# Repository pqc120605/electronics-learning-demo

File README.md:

# Mạch Mở — demo học Điện tử, Nhúng và IoT

Mạch Mở là website học miễn phí cho người mới. Khách có thể xem bài học, khám phá mô hình mạch 3D tương tác và thử đổi nhịp LED trong bài ESP32 mà không cần tài khoản. Khu `/admin` dành cho founder để xem thống kê phiên truy cập và tương tác.

## Trang công khai và không gian học

- Quyết định kiến trúc về dữ liệu dùng chung nằm trong [ADR 0001 · Node API tự quản](docs/adr/0001-backend-duy-nhat-node-api.md).
- `/` là trang giới thiệu thế giới điện tử và các tính năng của Mạch Mở.
- `/app` là dashboard học tập dành cho khách, dẫn tới bài học, thư viện board/linh kiện, bàn lắp mạch, chủ đề, công cụ và dự án đang có.
- App workspace là một bề mặt guest-first chạy chung SPA React/Vite với website. Đây chưa phải native app. Service worker cache app shell cùng các JS/CSS đã tải để mở lại một số route khi offline; không cache model 3D lớn, firmware hay API, và chưa có đồng bộ offline.
- Bản đồ sản phẩm Web/App, ranh giới dữ liệu, simulator providers, công cụ GitHub đã khảo sát và lộ trình nền tảng được mô tả trong [`docs/mach-mo-final-web-app-framework.md`](../docs/mach-mo-final-web-app-framework.md).
- Route chuẩn nằm trong `src/data/productRoutes.ts`; feature, trạng thái và nhãn menu dùng chung nằm ở `src/data/productFeatureRegistry.ts`. URL legacy như `/boards` và `/build` vẫn được giữ để tương thích; các đường dẫn app có namespace `/app/...`.
- Hợp đồng chuẩn hóa cho simulation provider nằm tại `src/simulation/contracts.ts`. Các bài học dùng interpreter giáo dục giới hạn trong `src/lib/simulationProviders.ts`; công cụ SPICE dùng `eecircuit-engine`/ngspice WASM trong Web Worker. Workspace có handoff cho subset analog khi dây, node và trị số thỏa mapping hỗ trợ; compiler từ chối MCU/GPIO và phần tử chưa có model. Đây không phải chuyển đổi mọi bài/schematic, không lấy copper PCB làm netlist và không thay provider firmware.
- Luồng CAD có báo cáo đối chiếu tất cả chân có net trong KiCad schematic với PCB IPC-D-356 theo ref/pin và nhóm kết nối; giữ rõ chân NC và bỏ qua record via khi đếm chân. Sau đó, đường tạo netlist SPICE vẫn chỉ ánh xạ R/C/L/V hỗ trợ và yêu cầu loại trừ tường minh phần tử khác. Xem [hướng dẫn nhập KiCad vào SPICE](docs/kicad-to-spice-import.md); đối chiếu CAD không xác nhận file cùng revision hoặc board sản xuất, và PCB đơn lẻ không tự trở thành mô hình điện.
- Các URL chức năng hiện tại như `/learn/esp32-led`, `/boards`, `/components`, `/build`, `/topics`, `/projects` và `/tools/firmware-hex` vẫn dùng trực tiếp được.
- Dashboard `/app` và trang `/topics` hiển thị lộ trình 4 chặng gồm đủ 11 bài (`src/data/learningPath.ts`); bài LED mở trang dài `/learn/esp32-led`, 10 bài còn lại mở trang chuẩn bị `/learn/<id>` với mục tiêu, board, bảng chân, vật tư và mức mô phỏng trước khi vào phòng thử. Thứ tự này cũng quyết định "bài tiếp theo" trong phòng thử. Sơ đồ nguyên lý có danh sách net nối dây; chọn net tô sáng các kết nối tương ứng trên schematic và cảnh lắp. Net ở đây chỉ là topology workspace, không phải ERC, kết quả điện hay copper của PCB tham chiếu. Board profile hiển thị các link tài liệu/ảnh/CAD được khai báo cho đúng mẫu và revision; link nguồn là bằng chứng tham khảo, không xác minh board vật lý người học đang cầm. Bài vừa mở và checklist tự xác nhận của bài LED được lưu cục bộ; đây không phải tiến độ kỹ năng đã xác minh và không đồng bộ tài khoản.
- Cả 11 bài thực hành đều có deep link `?lesson=<id>`, ví dụ `/build?lesson=button-led&guided=1`; khi mở từ `/app`, liên kết nội bộ giữ namespace app. Link bài mở phiên riêng theo tab trong `sessionStorage`, tiếp tục bản nháp của phiên nếu có và không thay workspace `/build` trong `localStorage`. Link `?board=` chỉ đề xuất đổi board khi đã có workspace.
- Công cụ **Kiểm tra firmware HEX** đọc tệp Intel HEX ngay trong trình duyệt, kiểm tra checksum/địa chỉ/kích thước và hiển thị các vùng dữ liệu. Có firmware assembly mẫu và HEX do Arduino IDE 2.3.10 + Arduino AVR Boards 1.8.8 biên dịch từ sketch Uno; AVR8js cho chọn Uno R3 hoặc Nano classic, yêu cầu xác nhận target ATmega328P và chạy tối đa một giây để quan sát GPIO D13/PB5. Tệp người dùng chọn không tải lên máy chủ; target không nhận dạng tự động; web không compile sketch Arduino hay upload, và các board MCU khác chưa được hỗ trợ.
- Trong workspace `/build`, panel **Kết quả đến từ đâu?** phân biệt trace của mô hình bài học với lần chạy HEX AVR8js và waveform trả về từ SPICE. Chế độ HEX là tùy chọn riêng, chỉ nhận Uno R3/Nano classic ATmega328P sau khi người dùng xác nhận target; chỉ hiển thị D13/PB5 và UART0, không ánh xạ lên LED ngoài trên canvas. Kết quả SPICE chỉ quay lại cùng revision workspace trong phiên tab; sửa board, bài, code hoặc dây sẽ dừng/loại kết quả cũ. Đây là quan sát từ provider riêng, không phải đồng mô phỏng firmware–SPICE hay điện áp đo trên board.
- Web manifest cung cấp tên ứng dụng, màu giao diện, biểu tượng và điểm mở `/app`. Tùy trình duyệt và thiết bị, người dùng có thể cài website như một ứng dụng web.
- Cache offline hiện chỉ giữ app shell và tài nguyên cùng origin đã tải. Lần đầu cần có mạng để cài cache; engine SPICE lớn được tải khi mở/chạy công cụ và khả năng dùng offline phụ thuộc cache của trình duyệt. Chưa có tài khoản học viên hay chạy firmware MCU tổng quát.

## Chạy trên máy

Yêu cầu Node.js tương thích với Vite 8.

```powershell
cd D:\StartupOS\electronics-learning-demo
npm.cmd install
npm.cmd run dev -- --host 127.0.0.1 --port 5173 --strictPort --open /build
```

Lệnh luôn dùng `http://127.0.0.1:5173/build`; nếu cổng 5173 đang bận, Vite báo lỗi thay vì âm thầm chuyển sang cổng khác. Đóng cửa sổ terminal đang chạy một bản Mach Mở cũ rồi thử lại. Giữ terminal mở khi dùng web; dừng server bằng `Ctrl+C`.

Trên Windows, có thể chạy `start-demo.cmd` bằng cách nhấp đúp. Script dùng `npm.cmd` để tránh lỗi PowerShell chặn `npm.ps1`, rồi mở workspace `/build` ở cổng cố định. Giữ cửa sổ terminal mở trong lúc dùng; đóng server bằng `Ctrl+C`.

`npm.cmd run build` chạy cổng kiểm tra phân phối trước khi tạo bản production. Ngspice WASM nay được tự build từ nguồn đã ghim; hồ sơ review gắn với hash nằm trong `public/licenses/spice-engine-provenance.json`. Dùng `npm.cmd run build:public` cho bản phát hành và giữ toàn bộ thư mục license/source/relink trong output. `build:local` vẫn chỉ là kiểm tra nội bộ, không thay thế release gate. Hướng dẫn mini PC Arch Linux: `docs/deployment/arch-mini-pc.md`.

Kiểm tra kiểu bằng `npm.cmd run typecheck`. Chạy smoke test trước khi thay đổi curriculum, parser hoặc topology bằng `npm.cmd test`. Bộ test chạy qua Node test runner và Vite SSR, không cần cổng localhost; nó kiểm tra dữ liệu bài/board, code mẫu, topology preset của cả mười một bài, một số luật nối mạch và việc biên dịch các page module. Nó chưa tự thao tác UI trên trình duyệt.

Để rà model board, dùng `npm.cmd run audit:board-models` cho hotspot/anchor/scene bounds và `npm.cmd run audit:board-model-geometry` để so mesh thân PCB từ STEP đã ghim SHA-256 với node PCB tách riêng trong GLB (hiện có 8 cặp nguồn). Kết quả CAD-to-CAD không thay thế đo board thật. `npm.cmd run audit:spice-engine` kiểm tra hash/runtime và giải mạch DC mẫu; `npm.cmd run check:public-release` vẫn fail-closed nếu thiếu provenance, inventory hoặc review đúng hash ngspice WASM.

## Kết nối Node API

Nội dung học và bàn lắp mạch chạy với chế độ khách. Đăng nhập Google/GitHub, cộng đồng online, góp ý và báo cáo quản trị dùng Node API qua `/api`, với PostgreSQL trên Mini PC. [Nối Vercel với Mini PC](docs/deployment/qd1-vercel-node-api.md) · [Cấu hình OAuth](docs/deployment/oauth-setup.md)

`.env.example` liệt kê các cờ bật giao diện cho từng môi trường. Sau khi API thông, bật các cờ tương ứng. Khóa OAuth và thông tin kết nối PostgreSQL cấu hình trên Mini PC. Quản trị cấp quyền theo email đã xác minh. [Cấu hình quyền xem dashboard](docs/deployment/dashboard-nhieu-website.md#quyền-xem-dashboard)

Analytics chỉ ghi mã phiên ngẫu nhiên theo tab, loại sự kiện trong allowlist, đường dẫn, component tùy chọn và thời gian máy chủ. Số phiên là ước tính, không phải số người thật được xác minh. Nhà cung cấp backend có thể xử lý metadata kỹ thuật để vận hành.

## Giới hạn demo

- View "Lắp mạch · 3D" trong phòng thử dựng cảnh từ GLB thật, có chọn linh kiện, callout, panel thông tin và luồng logic minh họa. Nhãn HIGH/LOW và hướng lấy từ chương trình và sơ đồ bài học, không phải điện áp hay dòng đo được. Linh kiện giữ đúng tỉ lệ và được tự xếp lên breadboard; chỉ các chân cùng net mới chung một dải. Đây là cách lắp gợi ý, chưa kiểm tra trên mạch thật. Chân của model tham số và Pico là vị trí minh họa.

- Trang Linh kiện và phòng thử hiển thị minh họa/mesh 3D theo hồ sơ từng linh kiện; model package KiCad là vỏ chuẩn, còn model tham số chỉ là hình khối giáo dục. Board Adafruit QT Py ESP32-C3 Rev B #5405 và Feather ESP32-S3 PID #5323 có viewer CAD riêng theo nguồn hãng. Feather hiển thị cả footprint chưa có mesh và để các mesh không đối chiếu được ở trạng thái chưa định danh. Chi tiết, nguồn và giấy phép ở `docs/component-model-registry.md` và `docs/board-model-sourcing.md`.

- Bài ESP32 có hai cảnh 3D: PCB theo thiết kế ESP32 Dev Kit Clone 30 chân có schematic/netlist, và cảnh lắp mạch học tập gồm board, breadboard, LED, điện trở 220 Ω cùng dây jumper. Chọn linh kiện để xem vai trò, net/pad liên quan và lưu ý an toàn. Thiết kế này đo khoảng 47,06 × 29,23 mm; không đại diện cho mọi board bán dưới tên DevKit V1. Phần breadboard và linh kiện ngoài là hình học minh họa, không phải netlist hay mô phỏng điện.
- Viewer dùng WebGL2 và đọc profile GLB KiCad của asset mẫu. Mô hình chỉ thể hiện hình học, không mô phỏng điện áp/dòng điện hay chạy firmware. Hiệu ứng LED nhấp nháy trong viewer bài học chỉ là phản hồi hình ảnh.
- PCB, schematic, thông tin nguồn và hướng dẫn tái tạo model nằm trong `assets/boards/esp32-devkit-v1-30pin/`; GLB phục vụ web nằm trong `public/models/`. Sau khi xuất lại PCB GLB bằng KiCad, chạy `python assets/boards/esp32-devkit-v1-30pin/compose_led_assembly.py` để dựng lại cảnh lắp ráp. U3 CP2102 dùng vỏ QFN KiCad cùng kích thước, không có marking mặt chip.
- Web không biên dịch code hoặc nạp code qua USB. AVR8js là runner giới hạn cho ATmega328P trên Uno R3/Nano classic, nhận firmware HEX đã biên dịch và quan sát D13/ngoại vi cơ bản; không phải mô phỏng điện tổng quát hay hỗ trợ ESP32/Pico/STM32.
- Các model Arduino Uno/Nano/Mega trên web đã được thay bằng hình học PCB từ CAD board tham chiếu, kèm package 3D cho MCU, một số linh kiện thụ động, LED và header. CAD nguồn, attribution, giới hạn và cách xuất lại ở `assets/boards/arduino-reference/README.md`.
- Project chưa đọc được không bị xóa khi lưu; trang Dự án cho tải bản sao phục hồi. Kiểm kê asset và trạng thái Git nằm ở `docs/asset-and-repo-inventory.md`.
- Bản đầu chưa có tài khoản học viên, đồng bộ hoặc xác minh tiến độ học tập, thanh toán hay cửa hàng kit. Lịch sử bài vừa mở và checklist tự xác nhận, project và bản nháp workspace được lưu cục bộ trên thiết bị.
- Bài mẫu nêu rõ loại board và giả định chân GPIO; hãy đối chiếu pinout của board thực tế trước khi nối dây.

### Cách đọc mức độ mô phỏng và độ tin cậy

- **Mô phỏng hành vi cơ bản**: parser chỉ hiểu một tập câu lệnh được liệt kê trong bài. Nó chuyển code thuộc tập đó thành trạng thái/luồng minh họa; không biên dịch hay chạy firmware.
- **Minh họa khái niệm**: hoạt động theo kịch bản định sẵn; code mẫu không được thực thi.
- **Mô hình tham chiếu · CAD theo revision**: hình học được dựng từ bộ CAD/revision đã ghi nguồn. Nhãn này không xác nhận board clone đang bán có cùng layout, BOM hay linh kiện thực tế.
- **Alias học tập / suy luận từ CAD**: vị trí/chân hoặc package chưa được xác minh hoàn toàn. Các linh kiện rời trong bàn lắp có thể là hình học giáo dục tham số, không phải model nhà sản xuất.

Danh mục `/boards` ghi revision, nguồn và trạng thái viewer; `/components` phân biệt linh kiện có trong topology bài mẫu, chỉ hiển thị và chỉ tra cứu. Trang thư viện board và trang học hiển thị provenance của model: trạng thái, revision, nguồn, giấy phép/ghi công, độ tin cậy và các điểm còn thiếu. Không nên hiểu “có model 3D” là đã xác thực mọi linh kiện hoặc mô phỏng điện chính xác.

## Bộ công cụ

- `/tools/electronics-calculators` và `/app/tools/calculators`: bộ tính điện trở LED, bộ chia áp ADC, pull-up I²C và mạch RC. Mỗi kết quả hợp lệ có thể mở netlist tương đương trong SPICE. Trong workspace, tab **Schematic**, **Lắp mạch 3D** và **PCB** có thể gửi topology dây tường minh cùng R/C/LED/diode/LDR và trị số đã khai báo sang bộ biên dịch analog; yêu cầu GND, nguồn và các chân phải nối đủ. Board MCU, code/firmware, copper CAD, ký sinh PCB và linh kiện không có mapping đều bị loại hoặc chặn với lý do cụ thể. Đây là circuit subset theo topology workspace, không phải mô phỏng toàn board. Kết quả cần đối chiếu datasheet trước khi lắp thật.
- `/tools/spice` và `/app/tools/spice`: netlist analog chạy bằng ngspice WASM trong Web Worker của trình duyệt. Có ví dụ DC, RC transient, diode; netlist tối đa 16 kB/160 dòng, tối đa 20.000 điểm ước tính và giới hạn kết quả solver 20.000 điểm, timeout 30 giây; xem đồ thị/bảng và xuất CSV. Hỗ trợ có giới hạn R/C/L, V/I, diode/BJT/MOSFET với model số khai báo trực tiếp; chỉ `.op`, `.tran`, `.ac`, `.dc`. Ngoài handoff từ workspace, có thể nhập **XML netlist xuất từ KiCad Eeschema**: chỉ R/C/L và nguồn V DC có trị số tĩnh được giữ; linh kiện khác phải loại trừ bằng thao tác rõ ràng, nguồn/chân GND cần có. File `.kicad_sch`/`.kicad_pcb`, copper, parasitic, IC/MCU và firmware không tự chuyển đổi. Không nhận file/include/control, không chạy firmware MCU và không phải công cụ xác nhận an toàn/phần cứng. Engine WASM tải riêng khoảng 4,52 MB khi mở công cụ.
- Engine tự build từ ngspice 45.2 commit `724dc77b9153dc75eaec474b1f7a44f1fcf5f362`, wrapper local `eecircuit-engine` 1.9.0-machmo.1. WASM khoảng 4,52 MB, kèm JS glue phù hợp. Nguồn, patch, notices, object/relink materials và review có trong [provenance](public/licenses/spice-engine-provenance.json), [notice](public/licenses/NGSPICE-NOTICE.txt) và `public/licenses/ngspice-selfbuild/`. Bản web tắt BSIM4 mới, HiSIM2/HV1/HV2, HICUM2, XSPICE, OSDI, CIDER, KLU, FFTW và PDK cards đóng gói; không coi các model bị tắt là được hỗ trợ.
- `postinstall` chạy `scripts/prepare-spice-engine.mjs`: kiểm SHA-256 của cả wrapper, parser, JS glue và WASM từ `vendor/mach-mo-spice`, rồi sao chép nguyên cặp vào `public/vendor/eecircuit-engine`. Cài lại dependency không khôi phục binary npm 1.8.0 cũ. Wrapper MIT không thay thế điều khoản của Numparam LGPL và các thành phần trong WASM.
- `/app/classroom-kits`: kế hoạch lớp/kit cục bộ, chọn board và revision tham chiếu, 1–100 trạm, bài học, số lượng kit, lưu ý an toàn, in phiếu, xuất CSV/JSON và nhập lại gói đã kiểm tra allowlist. Gói chia sẻ thủ công kèm link bài, nhãn năng lực mô phỏng, thông tin board/revision, nguồn board và ghi chú an toàn; chưa có upload/cloud, tài khoản lớp, bảng tin hay kiểm duyệt cộng đồng. Không thu dữ liệu học sinh.

## Thư viện board và bài học lập trình

- Trang Khám phá có tìm kiếm và lọc theo ESP, Arduino, STM32; có thể chọn tối đa ba board để so sánh MCU, revision, điện áp logic, ngoại vi, mục tiêu phù hợp, điểm đánh đổi và trạng thái model. Bảng cảnh báo khi mức logic khác nhau, có link nguồn, bỏ từng board và xóa lựa chọn. Thông tin preview luôn đi kèm nguồn và trạng thái xác minh.
- Bài LED có chế độ khối cho người mới, tạo code C++ từ các khối GPIO/chờ, và chế độ C++ riêng để tự luyện. Bản nháp code được giữ khi đổi chế độ; chỉ cú pháp thuộc tập con được hỗ trợ mới chuyển thành luồng minh họa. Cú pháp khác được giữ nguyên và tắt luồng, không chạy code trong trình duyệt.
- Luồng hoạt động chỉ minh họa câu lệnh, GPIO và trạng thái LED theo từng bước; không mô phỏng firmware, điện học hoặc thời gian thực.
- NUCLEO-F401RE vẫn là preview; ESP32-S3-DevKitC-1 PCB V1.1 đã có viewer 3D tái dựng giáo dục với 48 footprint/package mesh và 44 anchor J1/J3. Model S3 có lỗi DRC, phần lớn mesh là package chung, chưa kiểm chứng board thật và không dùng chế tạo; xem SOURCE.md/NOTICE. Board CAD viewers gồm Adafruit QT Py ESP32-C3 Rev B #5405, Feather ESP32-S3 #5323 (8 MB/no-PSRAM), Feather ESP32-S3 TFT #5483 (4 MB flash/2 MB PSRAM), Seeed Studio XIAO ESP32-S3 thường (STEP v2, CC BY-SA 4.0) và XIAO ESP32-C3 v1.3 (PCB KiCad, 68 footprint/47 package mesh tham khảo, bảng tra pad/net từ file PCB). Raspberry Pi Pico, Pico W, Pico 2 và Pico 2 H/SC1632 có viewer CAD riêng; cả bốn cho chọn 40 chân header J0 để tra cứu tĩnh. Tọa độ Pico/Pico W lấy trực tiếp từ Allegro; Pico 2/H kế thừa bố trí theo tài liệu Raspberry Pi và căn vào STEP tương ứng. Các viewer là tham khảo theo SKU/revision; phần lớn board khác chưa có pin picking/net highlighting hoặc mô phỏng. XIAO C3 có 14 chân header J1/J2 chọn được; pinout hãng chỉ ghép khi tên net CAD trùng chính xác D0–D10. QT Py #5405 có 14 pad JP1/JP3; Feather #5323 và #5483 có 28 pad JP1/JP3 mỗi board; các pad có thể chọn để xem net CAD và pinout của đúng PID. XIAO S3 thường có 14 pad J1/J2 chọn được trên model, tọa độ căn từ PCB Seeed OPL sang STEP (revision OPL chưa xác định; không khẳng định net route của mọi board). ESP32 DevKit clone cụ thể có 30 chân header chọn được theo thiết kế nguồn Brij Modi; không áp dụng cho mọi board bán dưới tên DevKit V1. Mọi lựa chọn chân này chỉ mở thông tin tĩnh, không tạo netlist hoặc tô đường đồng/net theo firmware. Hồ sơ CAD, hash, ghi công và giới hạn nằm trong `public/cad/`, `public/models/*.NOTICE.txt` và `docs/board-model-sourcing.md`. Thiết kế Blue Pill-style của SinaKarvandi đã lưu trữ ngoài `public/`, không phát hành viewer trong UI.

## Chủ đề, dự án và bàn lắp mạch

- `/topics` là bản đồ học gồm điện tử cơ bản, GPIO/lập trình nhúng, cảm biến/IoT và board/MCU. Mỗi chủ đề dẫn tới nội dung đang dùng được trong demo.
- `/projects` liệt kê mười một bài theo curriculum schema dùng chung: mục tiêu, thời lượng, board profile, linh kiện, an toàn và giới hạn mô phỏng. Tám bài dùng parser code subset giới hạn; ba bài nguồn/motor/MOSFET dùng kịch bản khái niệm cố định. Biến trở nhận đầu vào analog ảo chuẩn hóa 0–100. Bài LDR dùng đường cong giáo dục 100 kΩ khi tối → 1 kΩ khi sáng, R cố định 10 kΩ và VCC giả định 3,3 V để tính Vout/đầu vào chuẩn hóa; không tính lux, đặc tuyến cảm biến thật hay số đếm ADC vật lý. Thermistor vẫn là nội dung tham khảo.
- `/build` là workspace lắp ráp giáo dục. Có 28 board profile, thư viện linh kiện tìm kiếm và mười một bài mẫu: LED, nút, IR, HC-SR04 ảo, biến trở analog, LDR, LED 7 đoạn, nguồn + LED, so sánh buck/boost, motor qua TB6612FNG và MOSFET low-side. Dây lưu theo `partId`/`pinId`; validator có kiểm tra endpoint, dây trùng, một số nối nguồn/ngõ ra trực tiếp, cực tính sơ bộ, nhánh LED thiếu điện trở, một số cảnh báo theo board 3,3 V và topology của mười một bài theo net và loại linh kiện. Đây vẫn là heuristic giáo dục, chưa phải ERC tổng quát. Breadboard chỉ có bốn node logic (rail+, rail−, hàng A/B); chưa mô phỏng nhóm lỗ thực tế hoặc suy luận đầy đủ mạch nhiều nhánh/tự do. Parser có sáu mẫu cú pháp code và được dùng ở tám bài. Bài biến trở ánh xạ input ảo thành 0–100; bài LDR tính bộ chia áp giáo dục từ đường cong điện trở giả định và hiện Vout/giá trị analog chuẩn hóa. Bài LDR không tính lux, đặc tuyến linh kiện thật hay số đếm ADC vật lý. Ba bài nguồn/motor/MOSFET dùng kịch bản khái niệm cố định; sửa code sẽ bị từ chối, code chú thích không phải firmware. Các bài khái niệm hiển thị quan hệ buck/boost, lệnh chiều/PWM hoặc trạng thái Gate, không tính điện áp thật, dòng, ripple, hiệu suất, tốc độ, mô-men, nhiệt hay xung áp. Khi chạy từng bước, các dây và linh kiện thuộc nhánh minh họa được tô sáng đồng bộ ở canvas 2D và bàn lắp 3D; đây là hoạt ảnh luồng khái niệm, không phải mô phỏng dòng điện. Các component 3D trên bàn lắp là hình khối minh họa tham số, không phải CAD của nhà sản xuất. Dây tự nối không đồng nghĩa mô phỏng điện.
- Bàn lắp có tab **Sơ đồ nguyên lý** dùng cùng danh sách linh kiện và kết nối ổ định `partId`/`pinId` với các chế độ lắp mạch. Có thể kéo nền để pan, kéo linh kiện, nối/gỡ dây, chọn dây trên canvas hoặc danh sách để highlight, xoay biểu tượng, di chuyển bằng phím mũi tên và phóng to/thu nhỏ; luồng bài học tô sáng dây và linh kiện liên quan. Đây là sơ đồ học tập kiểu KiCad, chưa có quy tắc ký hiệu chuẩn đầy đủ, thuộc tính điện của dây, ERC, netlist điện hay xuất file CAD.
- Thẻ linh kiện trong `/components` và bảng chọn linh kiện ở `/build` dùng chung hình SVG giáo dục để nhận diện nhanh. Hình không phải ảnh sản phẩm hoặc model CAD; pin, trị số và hành vi cụ thể vẫn cần kiểm tra theo datasheet của linh kiện thật.
- Chi tiết linh kiện có mục **Tài liệu tham khảo** cho một nhóm board/chip/module thông dụng. Link ghi rõ đó là tài liệu board, datasheet chip hay hướng dẫn module; tài liệu của chip không xác minh breakout, clone hoặc sơ đồ chân của mọi module. Mục chưa có nguồn phù hợp sẽ nói rõ chưa gắn tài liệu thay vì tự suy diễn.
- Danh sách linh kiện có thể lọc theo nhóm và tình trạng tài liệu. Khi bộ lọc loại linh kiện làm mục đang chọn biến mất khỏi danh sách, phần chi tiết tự chuyển sang mục hợp lệ đầu tiên hoặc trạng thái rỗng.
- Mười bốn model board-reference có viewer 3D đang phát hành: ESP32 DevKit V1 clone 30 chân, ESP32-S3-DevKitC-1 V1.1, Arduino Uno R3, Nano classic, Mega 2560 R3, Raspberry Pi Pico, Pico W, Pico 2, Pico 2 H/SC1632, Adafruit QT Py ESP32-C3 Rev B #5405, Feather ESP32-S3 #5323, Feather ESP32-S3 TFT #5483, Seeed Studio XIAO ESP32-S3 thường và Seeed XIAO ESP32-C3 v1.3. Bốn board ESP32/Arduino có manifest PCB 2D theo lớp đồng; ESP32-S3-DevKitC-1 cùng bốn board Pico, ba board Adafruit và hai board XIAO (ESP32-S3, ESP32-C3) là viewer 3D tham chiếu chưa có lớp đồng. Pico family có 40 chân J0 chọn được để tra cứu; anchor Pico/Pico W lấy từ Allegro, còn Pico 2/Pico 2 H dùng bố trí kế thừa đã ghi rõ. ESP32 DevKit clone có 30 chân header chọn được từ anchor theo CAD nguồn của đúng clone; XIAO ESP32-C3 có 14 chân J1/J2, QT Py có 14 pad JP1/JP3, Feather #5323/#5483 mỗi board có 28 pad JP1/JP3 chọn được để tra cứu pinout/net tĩnh theo đúng variant. XIAO ESP32-S3 thường có 14 anchor pad J1/J2 từ PCB Seeed OPL để chọn trên 3D; GPIO/chức năng theo guide hiện hành, revision OPL chưa rõ và chưa xác nhận board thật. Các lựa chọn chân trên board CAD-only không tạo netlist hoặc tô đồng/net tương tác. C3 có 68 footprint chọn được, 47 mesh package tham khảo; các mesh package không phải hình marking chính xác của part. Thiết kế STM32F103 custom của SinaKarvandi đã lưu trữ ngoài `public/`, không phát hành trên UI. Viewer 2D hỗ trợ mặt trên/dưới, pan/zoom, chọn linh kiện/pad/net. Chỉ mapping D13/SCK của Uno được dùng để liên kết với tín hiệu bài. Đường tô net không mô phỏng dòng điện, điện áp hay firmware. Nguồn, checksum, mức xác minh và checklist tiếp nhận board mới ở `docs/board-model-sourcing.md`.
- Danh mục hiện có 28 hồ sơ board và 58 mục linh kiện. Mười bốn board có viewer CAD 3D, trong đó bốn board có thêm lớp đồng PCB 2D. `public/models/` có mười lăm GLB: mười bốn board tham chiếu và một cảnh lắp ráp bài học. Một số mesh chưa khớp designator được giữ ở trạng thái chưa định danh; không coi viewer là xác nhận board ngoài đời.

## Luồng sử dụng cho người mới

- Trang đầu giới thiệu khái niệm điện tử qua luồng cảm biến → vi điều khiển → thiết bị, rồi chỉ ra bài học, thư viện và phòng thử.
- Điều hướng được gom theo các mục **Giới thiệu**, **Không gian học**, **Thư viện** (board/linh kiện), **Phòng thử**, **Công cụ** và **Lộ trình** (chủ đề/dự án). Công cụ HEX kiểm tra Intel HEX trên trình duyệt và có spike AVR8js riêng cho ATmega328P; công cụ không nhận diện MCU từ HEX và không nạp board.
- Công cụ firmware có ba artifact: HEX bare-metal assembly, sketch Arduino `.ino`, và HEX Uno đã được Arduino IDE biên dịch (FQBN `arduino:avr:uno`). HEX Arduino đã được chạy thử trong AVR8js và quan sát D13 chuyển LOW → HIGH → LOW. Trước khi chạy HEX bằng AVR8js, người dùng vẫn phải xác nhận target ATmega328P vì định dạng Intel HEX không mã hóa MCU đích.
- Trang đầu có một CTA chính dẫn tới bài LED nhập môn, không yêu cầu tài khoản hay kinh nghiệm; các đường dẫn phụ gom thành tối đa bốn lựa chọn.
- `/build` có bốn bước có thể nhảy tự do: **Chọn bài → Lắp mạch → Viết code → Chạy và quan sát**. Bước đầu hiển thị mười một thẻ bài học, mục tiêu, độ khó, thời lượng và kiểu mô phỏng; chọn thẻ sẽ nạp preset tương ứng. Bước chỉ thay đổi phần công cụ đang xem, không xóa mạch, dây, board, code hay đầu vào mô phỏng.
- Bài LED có khối kéo thả và C++ tự luyện. Mỗi chế độ giữ bản nháp riêng; code C++ chỉnh tay không tự biến ngược thành khối. Parser/mô phỏng vẫn chỉ hỗ trợ tập cú pháp giáo dục đã mô tả, không thực thi firmware; bài LED chỉ nhận thứ tự ghi mức → delay → ghi mức → delay trong `loop()`.
- Bài analog dùng `map(analogRead(chân), 0, ADC_MAX, 0, 100)` với dải đã xác minh: 0–1023 cho Uno, Nano classic, Mega; 0–4095 cho ESP32 DevKit. Board khác bị khóa bài analog. Bài LED 7 đoạn chỉ mở trên bốn board này. Bài cũng khóa khi chân đầu vào trùng chân LED. Chi tiết ở `docs/MACH-MO-MVP-STATUS.md`.
- GPIO hiển thị theo code; LED chỉ sáng khi mạch không có lỗi. Mạch thành lỗi khi đang chạy thì mô phỏng dừng.
- Dưới tiêu đề mỗi bước có panel **Việc cần làm tiếp theo**: nêu một việc, cách sửa và nút hành động theo trạng thái thật của mạch, code và board. Bấm Chạy thất bại sẽ đưa focus tới panel này. Khi đã có kết quả chạy, panel có nút sang bài kế tiếp.
- Nút **Hướng dẫn sử dụng** trong phòng thử đưa tới hướng dẫn nhanh; từ bài học và các trang thư viện có đường dẫn trực tiếp về bước tiếp theo.

## Phạm vi simulator hiện tại

- Công cụ SPICE nhận netlist nhập trực tiếp, các bộ tính tương đương, topology analog subset từ workspace, XML netlist KiCad Eeschema và một luồng hạn chế ghép IPC-D-356 với XML schematic. Luồng ghép chỉ đưa R/C/L/V hai chân qua khi pin/net khớp, đơn vị trị số hợp lệ và phần không hỗ trợ được loại trừ tường minh. PCB CAD đơn lẻ không chứa đủ thông tin điện để tự chuyển; muốn mô phỏng toàn board phải có schematic/netlist, model, BOM/variant và mọi phần tử cần thiết.
- Bước mở rộng simulator hành vi: thêm LDR/thermistor vào luồng analog ảo hoặc mở rộng parser theo board sau khi xác minh profile và công bố giới hạn rõ.
- Chạy firmware thực cần provider riêng. Wokwi có phạm vi MCU/linh kiện rộng nhưng tích hợp vào sản phẩm cần kiểm tra quyền thương mại/API và việc chuyển code người học. QEMU/Espressif phù hợp một số MCU nhưng cần runtime/backend; Renode hỗ trợ nhiều board embedded nhưng cần platform/peripheral model và hạ tầng riêng. Arduino CLI chỉ compile/upload, còn KiCad xuất model 3D chứ không mô phỏng MCU.
- Quyết định kiến trúc, so sánh phương án và nguồn chính thức nằm trong `docs/superpowers/specs/2026-10-30-web-simulation-provider-adr.md`.

- Bài biến trở analog có block kéo thả, điều chỉnh ngưỡng sinh code, C++ draft riêng, sắp xếp block bằng kéo hoặc nút bàn phím, và chặn luồng khi thứ tự block sai. Ngưỡng được dùng đồng nhất cho C++ mẫu, parser, trace và trạng thái LED. Đầu vào chuẩn hóa 0–100 vẫn chỉ là dữ liệu mô phỏng giáo dục.

- Bài nút nhấn và IR nay có block kéo thả theo luồng đọc → điều kiện → LED, C++ draft riêng cho từng bài và lưu trạng thái riêng trong localStorage. Sai thứ tự block chặn chạy; chỉ code trong parser giáo dục giới hạn mới được diễn giải thành trace.
- Chọn thẻ bài học đưa người mới tới bước lắp mạch; số lượng thẻ lấy động từ curriculum và hướng dẫn nhanh liệt kê chính xác các bài có block.

- C++ nháp lưu theo từng bài và board; đổi bài/board tải nháp phù hợp hoặc mẫu đúng pin profile, không ghi đè nháp ở board khác. Có nút khôi phục code mẫu; “Đặt lại bài” reset mạch và đầu vào nhưng vẫn giữ bản nháp cũ để phục hồi.

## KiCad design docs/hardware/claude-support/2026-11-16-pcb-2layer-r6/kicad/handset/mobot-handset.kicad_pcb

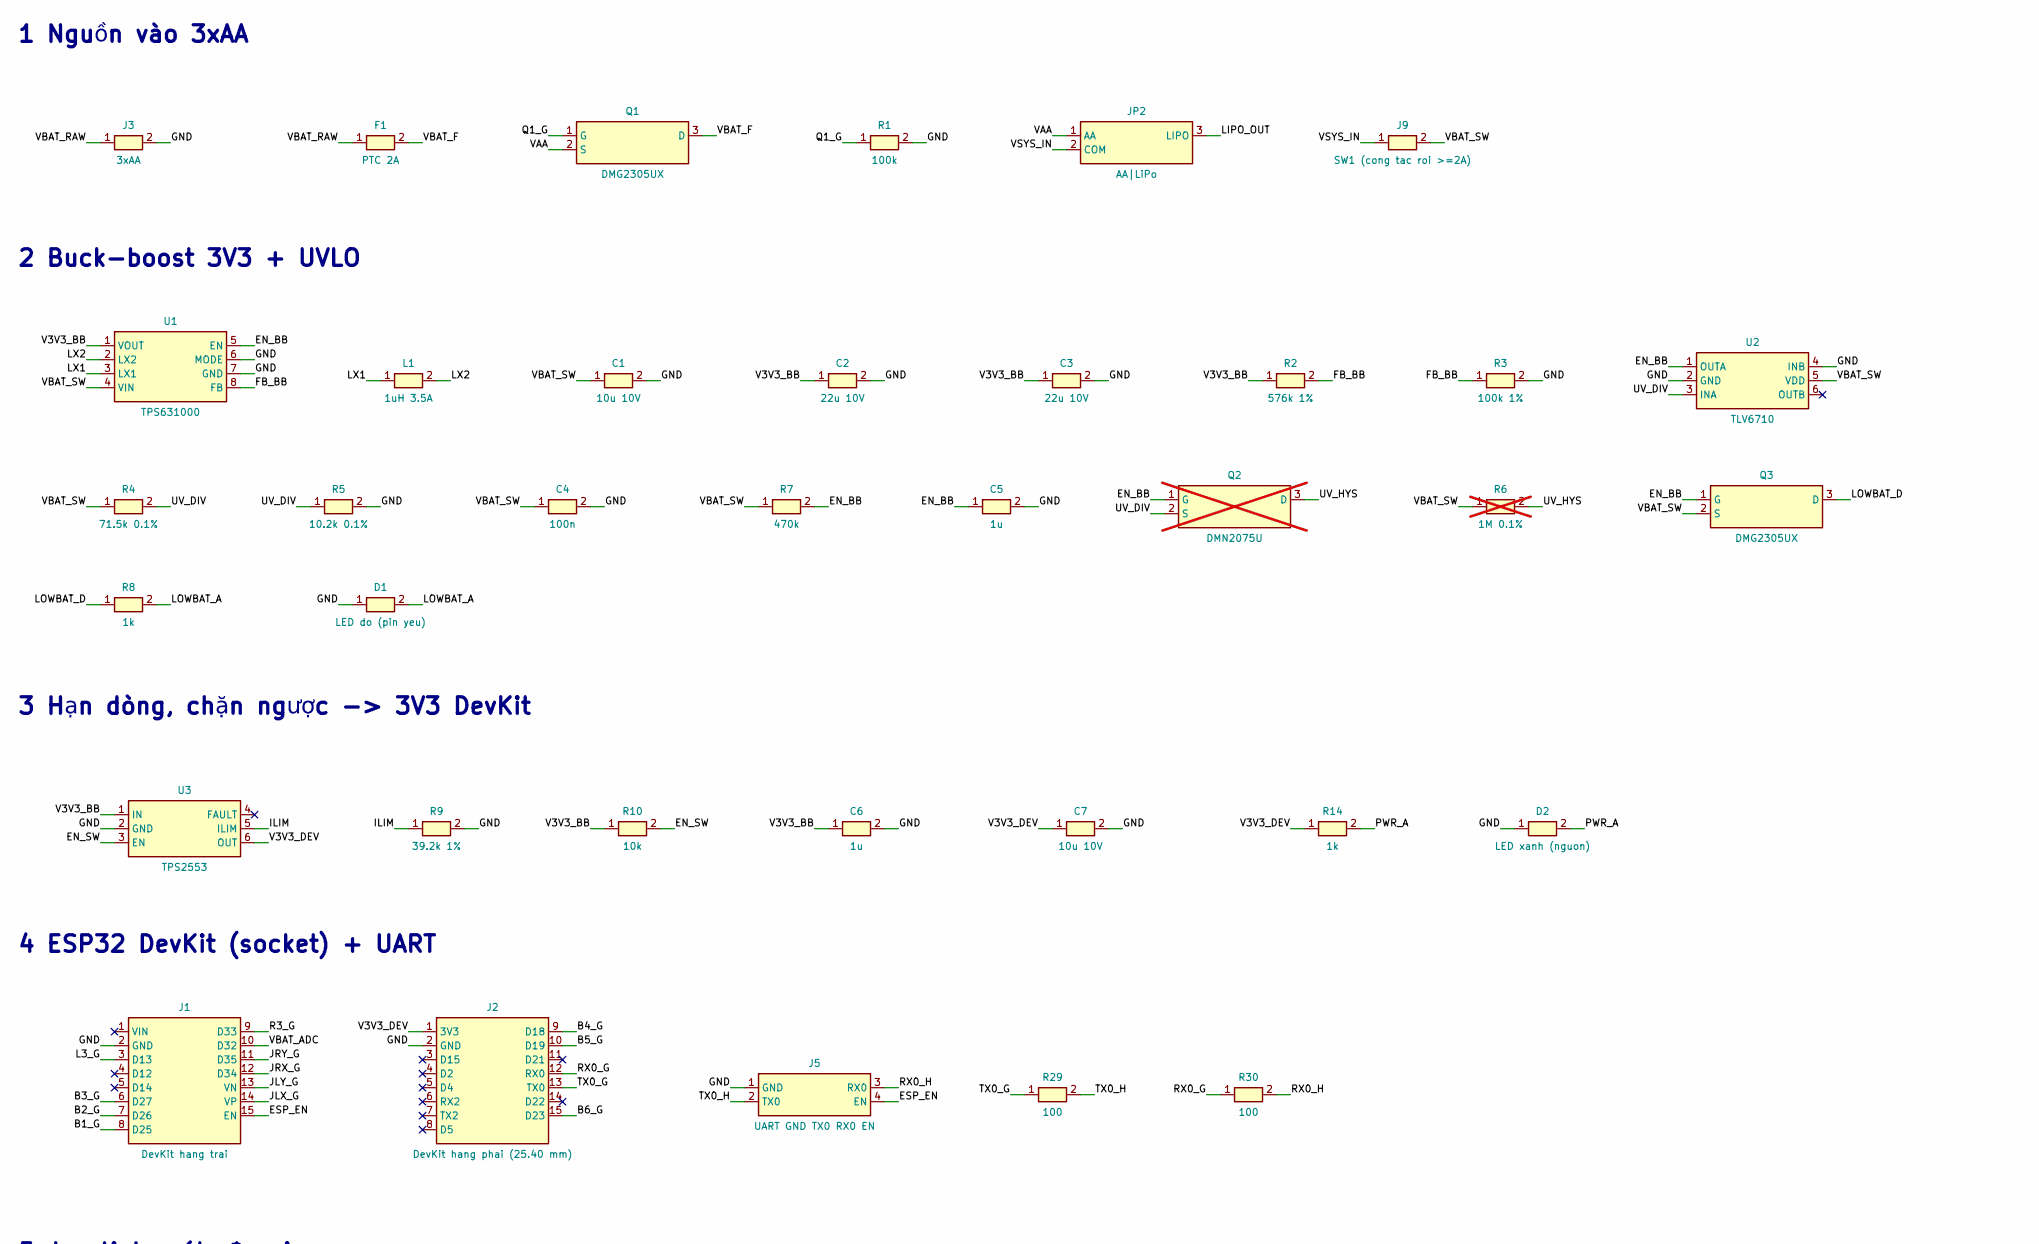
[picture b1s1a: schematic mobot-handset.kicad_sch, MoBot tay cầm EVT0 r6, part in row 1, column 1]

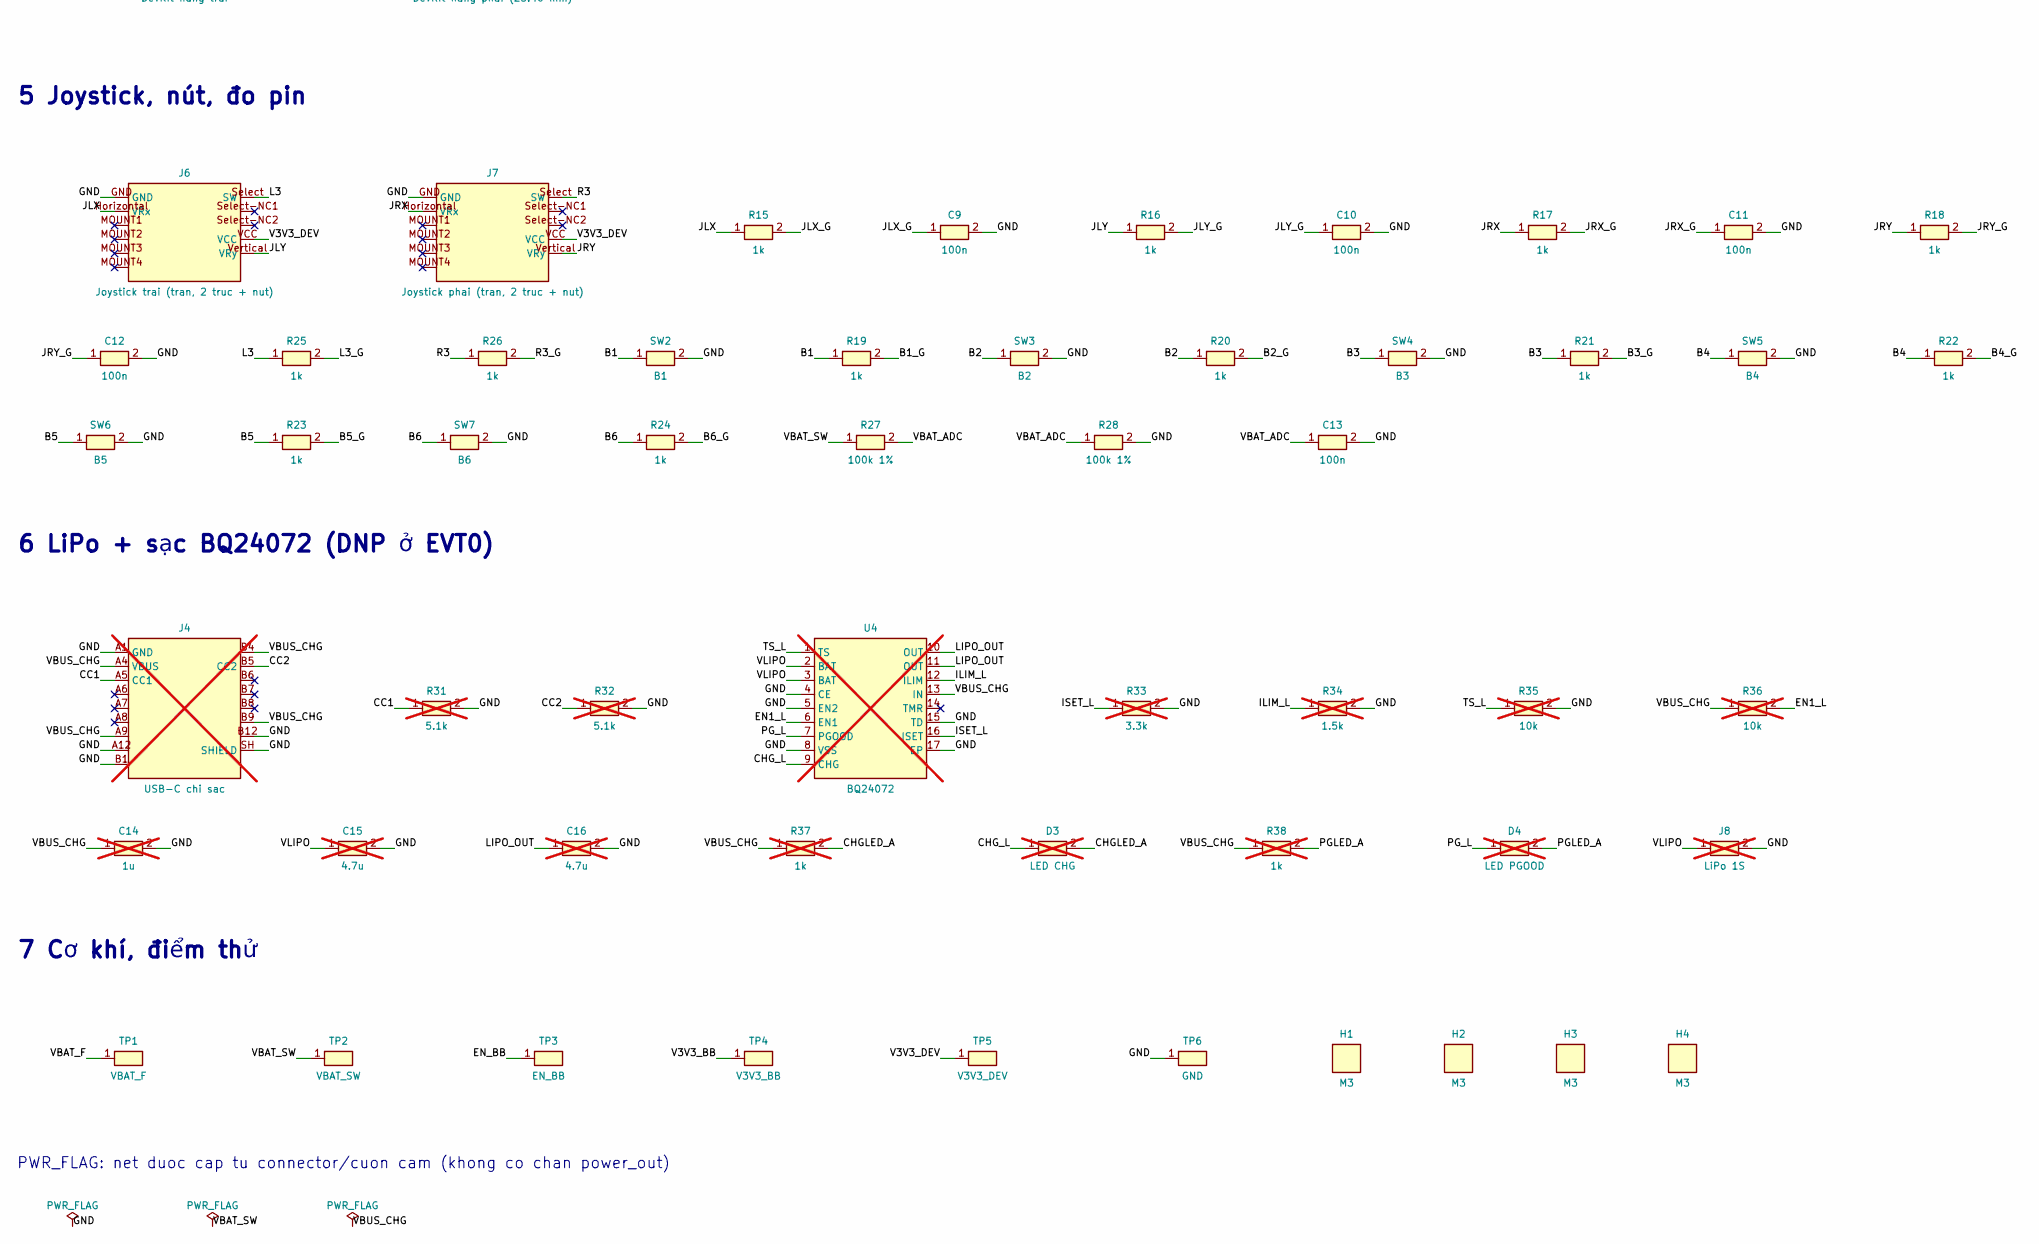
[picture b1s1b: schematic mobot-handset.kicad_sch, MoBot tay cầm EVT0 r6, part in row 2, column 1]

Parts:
C1, C7: 10u 10V; C_0805_2012Metric
C2, C3: 22u 10V; C_0805_2012Metric
C4, C9, C10, C11, C12, C13: 100n; C_0603_1608Metric
C5, C6: 1u; C_0603_1608Metric
C14: 1u; C_0603_1608Metric; not fitted
C15, C16: 4.7u; C_0603_1608Metric; not fitted
D1: LED do (pin yeu); LED_0603_1608Metric
D2: LED xanh (nguon); LED_0603_1608Metric
D3: LED CHG; LED_0603_1608Metric; not fitted
D4: LED PGOOD; LED_0603_1608Metric; not fitted
F1: PTC 2A; Fuse_1812_4532Metric; MPN MF-MSMF200/8X
H1, H2, H3, H4: M3; MountingHole_3.2mm_M3
J1: DevKit hang trai; PinSocket_1x15_P2.54mm_Vertical
J2: DevKit hang phai (25.40 mm); PinSocket_1x15_P2.54mm_Vertical
J3: 3xAA; JST_XH_B2B-XH-A_1x02_P2.50mm_Vertical; MPN B2B-XH-A
J4: USB-C chi sac; USB_C_Receptacle_GCT_USB4105-xx-A_16P_TopMnt_Horizontal; MPN USB4105-GF-A; not fitted
J5: UART GND TX0 RX0 EN; PinHeader_1x04_P2.54mm_Vertical
J6: Joystick trai (tran, 2 truc + nut); Joystick_PTH
J7: Joystick phai (tran, 2 truc + nut); Joystick_PTH
J8: LiPo 1S; JST_PH_B2B-PH-K_1x02_P2.00mm_Vertical; MPN B2B-PH-K-S; not fitted
J9: SW1 (cong tac roi >=2A); JST_XH_B2B-XH-A_1x02_P2.50mm_Vertical; MPN B2B-XH-A
JP2: AA|LiPo; SolderJumper-3_P1.3mm_Bridged12_RoundedPad1.0x1.5mm
L1: 1uH 3.5A; L_Changjiang_FNR4030S; MPN XEL4030-102ME
Q1, Q3: DMG2305UX; SOT-23; MPN DMG2305UX-7
Q2: DMN2075U; SOT-23; MPN DMN2075U-7; not fitted
R1: 100k; R_0603_1608Metric
R2: 576k 1%; R_0603_1608Metric
R3, R27, R28: 100k 1%; R_0603_1608Metric
R4: 71.5k 0.1%; R_0603_1608Metric
R5: 10.2k 0.1%; R_0603_1608Metric
R6: 1M 0.1%; R_0603_1608Metric; not fitted
R7: 470k; R_0603_1608Metric
R8, R14, R15, R16, R17, R18, R19, R20, R21, R22, R23, R24, R25, R26: 1k; R_0603_1608Metric
R9: 39.2k 1%; R_0603_1608Metric
R10: 10k; R_0603_1608Metric
R29, R30: 100; R_0603_1608Metric
R31, R32: 5.1k; R_0603_1608Metric; not fitted
R33: 3.3k; R_0603_1608Metric; not fitted
R34: 1.5k; R_0603_1608Metric; not fitted
R35, R36: 10k; R_0603_1608Metric; not fitted
R37, R38: 1k; R_0603_1608Metric; not fitted
SW2: B1; SW_PUSH_6mm
SW3: B2; SW_PUSH_6mm
SW4: B3; SW_PUSH_6mm
SW5: B4; SW_PUSH_6mm
SW6: B5; SW_PUSH_6mm
SW7: B6; SW_PUSH_6mm
TP1: VBAT_F; TestPoint_Pad_D1.5mm
TP2: VBAT_SW; TestPoint_Pad_D1.5mm
TP3: EN_BB; TestPoint_Pad_D1.5mm
TP4: V3V3_BB; TestPoint_Pad_D1.5mm
TP5: V3V3_DEV; TestPoint_Pad_D1.5mm
TP6: GND; TestPoint_Pad_D1.5mm
U1: TPS631000; SOT-583-8; MPN TPS631000DRLR
U2: TLV6710; TSOT-23-6; MPN TLV6710DDCR
U3: TPS2553; SOT-23-6; MPN TPS2553DBVR
U4: BQ24072; VQFN-16-1EP_3x3mm_P0.5mm_EP1.68x1.68mm; MPN BQ24072RGTR; not fitted

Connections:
/B1: R19.1, SW2.1
/B1_G: J1.8 (D25), R19.2
/B2: R20.1, SW3.1
/B2_G: J1.7 (D26), R20.2
/B3: R21.1, SW4.1
/B3_G: J1.6 (D27), R21.2
/B4: R22.1, SW5.1
/B4_G: J2.9 (D18), R22.2
/B5: R23.1, SW6.1
/B5_G: J2.10 (D19), R23.2
/B6: R24.1, SW7.1
/B6_G: J2.15 (D23), R24.2
/CC1: J4.A5 (CC1), R31.1
/CC2: J4.B5 (CC2), R32.1
/CHGLED_A: D3.2 (A), R37.2
/CHG_L: D3.1 (K), U4.9 (CHG)
/EN1_L: R36.2, U4.6 (EN1)
/EN_BB: C5.1, Q2.1 (G), Q3.1 (G), R7.2, TP3.1, U1.5 (EN), U2.1 (OUTA)
/EN_SW: R10.2, U3.3 (EN)
/ESP_EN: J1.15 (EN), J5.4 (EN)
/FB_BB: R2.2, R3.1, U1.8 (FB)
/GND: C1.2, C2.2, C3.2, C4.2, C5.2, C6.2, C7.2, C9.2, C10.2, C11.2, C12.2, C13.2, C14.2, C15.2, C16.2, D1.1 (K), D2.1 (K), J1.2 (GND), J2.2 (GND), J3.2 (-), J4.A1 (GND), J4.A12, J4.B1, J4.B12, J4.SH (SHIELD), J5.1 (GND), J6.GND, J7.GND, J8.2 (-), R1.2, R3.2, R5.2, R9.2, R28.2, R31.2, R32.2, R33.2, R34.2, R35.2, SW2.2, SW3.2, SW4.2, SW5.2, SW6.2, SW7.2, TP6.1, U1.6 (MODE), U1.7 (GND), U2.2 (GND), U2.4 (INB), U3.2 (GND), U4.4 (CE), U4.5 (EN2), U4.8 (VSS), U4.15 (TD), U4.17 (EP)
/ILIM: R9.1, U3.5 (ILIM)
/ILIM_L: R34.1, U4.12 (ILIM)
/ISET_L: R33.1, U4.16 (ISET)
/JLX: J6.Horizontal (VRx), R15.1
/JLX_G: C9.1, J1.14 (VP), R15.2
/JLY: J6.Vertical (VRy), R16.1
/JLY_G: C10.1, J1.13 (VN), R16.2
/JRX: J7.Horizontal (VRx), R17.1
/JRX_G: C11.1, J1.12 (D34), R17.2
/JRY: J7.Vertical (VRy), R18.1
/JRY_G: C12.1, J1.11 (D35), R18.2
/L3: J6.Select (SW), R25.1
/L3_G: J1.3 (D13), R25.2
/LIPO_OUT: C16.1, JP2.3 (LIPO), U4.10 (OUT), U4.11 (OUT)
/LOWBAT_A: D1.2 (A), R8.2
/LOWBAT_D: Q3.3 (D), R8.1
/LX1: L1.1, U1.3 (LX1)
/LX2: L1.2, U1.2 (LX2)
/PGLED_A: D4.2 (A), R38.2
/PG_L: D4.1 (K), U4.7 (PGOOD)
/PWR_A: D2.2 (A), R14.2
/Q1_G: Q1.1 (G), R1.1
/R3: J7.Select (SW), R26.1
/R3_G: J1.9 (D33), R26.2
/RX0_G: J2.12 (RX0), R30.1
/RX0_H: J5.3 (RX0), R30.2
/TS_L: R35.1, U4.1 (TS)
/TX0_G: J2.13 (TX0), R29.1
/TX0_H: J5.2 (TX0), R29.2
/UV_DIV: Q2.2 (S), R4.2, R5.1, U2.3 (INA)
/UV_HYS: Q2.3 (D), R6.2
/V3V3_BB: C2.1, C3.1, C6.1, R2.1, R10.1, TP4.1, U1.1 (VOUT), U3.1 (IN)
/V3V3_DEV: C7.1, J2.1 (3V3), J6.VCC, J7.VCC, R14.1, TP5.1, U3.6 (OUT)
/VAA: JP2.1 (AA), Q1.2 (S)
/VBAT_ADC: C13.1, J1.10 (D32), R27.2, R28.1
/VBAT_F: F1.2, Q1.3 (D), TP1.1
/VBAT_RAW: F1.1, J3.1 (+)
/VBAT_SW: C1.1, C4.1, J9.2 (OUT), Q3.2 (S), R4.1, R6.1, R7.1, R27.1, TP2.1, U1.4 (VIN), U2.5 (VDD)
/VBUS_CHG: C14.1, J4.A4 (VBUS), J4.A9, J4.B4, J4.B9, R36.1, R37.1, R38.1, U4.13 (IN)
/VLIPO: C15.1, J8.1 (+), U4.2 (BAT), U4.3 (BAT)
/VSYS_IN: J9.1 (IN), JP2.2 (COM)

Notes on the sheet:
1 Nguồn vào 3xAA
2 Buck-boost 3V3 + UVLO
3 Hạn dòng, chặn ngược -> 3V3 DevKit
4 ESP32 DevKit (socket) + UART
5 Joystick, nút, đo pin
6 LiPo + sạc BQ24072 (DNP ở EVT0)
7 Cơ khí, điểm thử
PWR_FLAG: net duoc cap tu connector/cuon cam (khong co chan power_out)

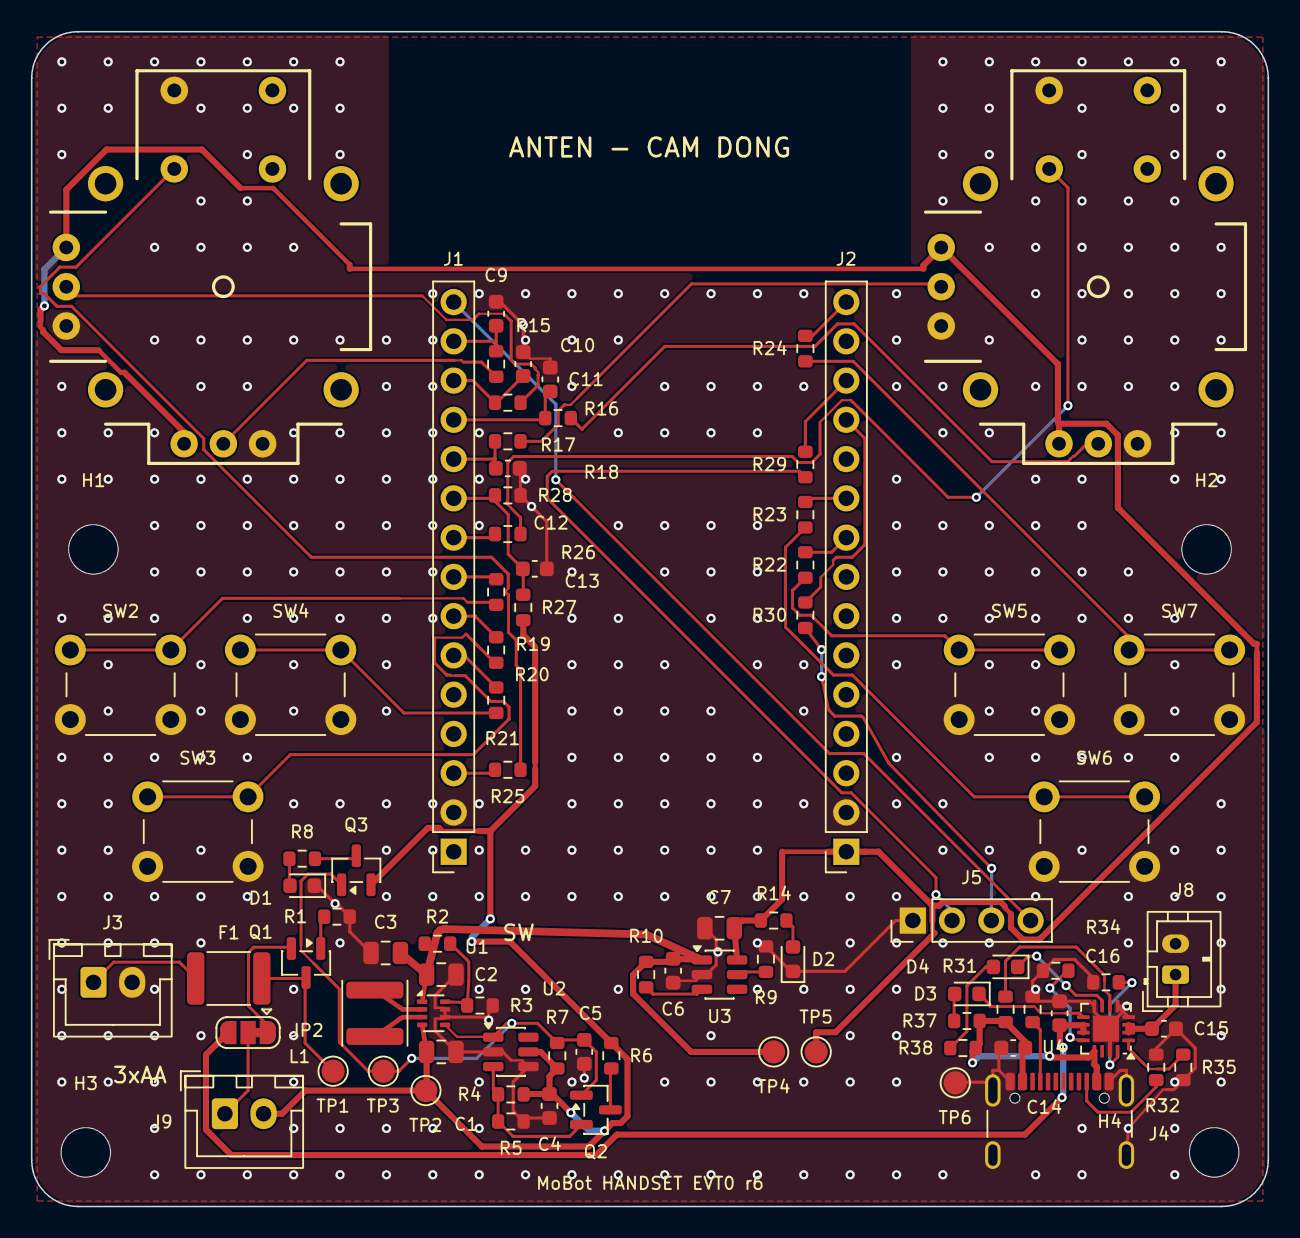
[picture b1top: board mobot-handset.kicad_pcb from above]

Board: 2 copper layers, 80.0 x 76.0 mm, 89 parts (0 on the bottom side), 63 nets.
